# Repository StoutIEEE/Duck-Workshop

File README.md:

# Duck workshop

This repo is to archive the files required for the flashing duck workshop. The workshop's existence was at first an April fools day joke. It eventually became a real workshop.

In this repo you can find:
 + The eagle files for first and second version of circuit
 + The workshop presentation with notes
 + A BOM for the second version of the circuit (the final version)

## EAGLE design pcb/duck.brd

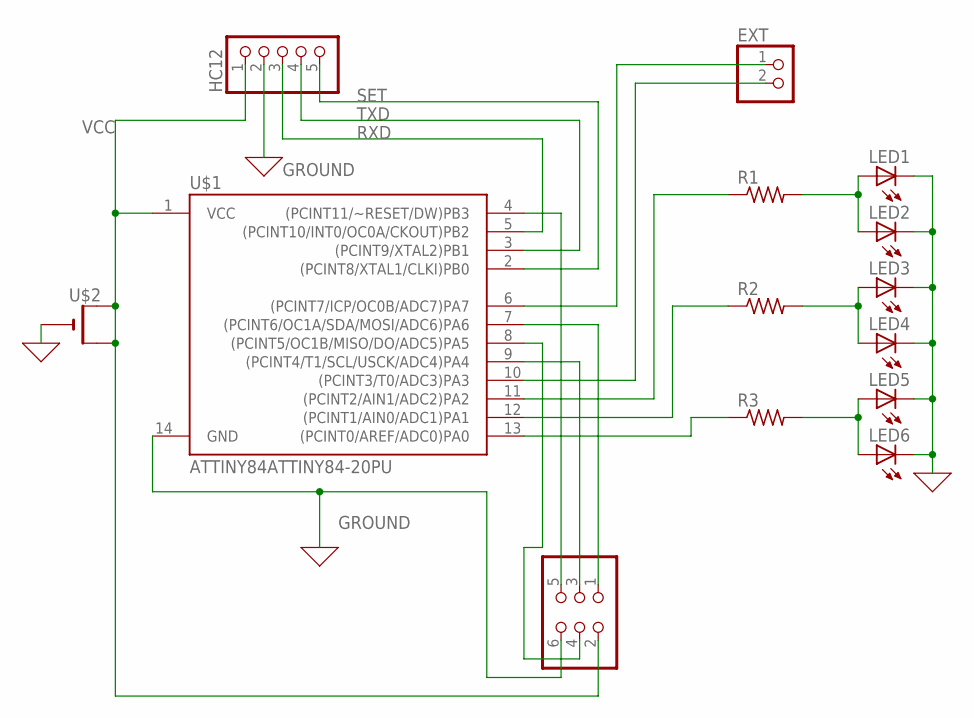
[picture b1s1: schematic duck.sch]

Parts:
DEV: PINHD-2X3; 2X03
EXT: PINHD-1X2; 1X02
HC12: PINHD-1X5; 1X05
LED1, LED2, LED3, LED4, LED5, LED6: LED3MM
R1, R2, R3: R-US_0204/7; 0204/7
U$1: ATTINY84ATTINY84-20PU; DIP14
U$2: CR1220THM; CR1220-THM

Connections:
GROUND: DEV.6, HC12.2, LED1.K (C), LED2.K (C), LED3.K (C), LED4.K (C), LED5.K (C), LED6.K (C), U$1.14 (GND), U$2.-
unnamed: DEV.1, U$1.7 ((PCINT6/OC1A/SDA/MOSI/ADC6)PA6)
unnamed: DEV.4, U$1.8 ((PCINT5/OC1B/MISO/DO/ADC5)PA5)
unnamed: DEV.3, U$1.9 ((PCINT4/T1/SCL/USCK/ADC4)PA4)
unnamed: R1.1, U$1.11 ((PCINT2/AIN1/ADC2)PA2)
unnamed: DEV.5, U$1.4 ((PCINT11/~RESET/DW)PB3)
unnamed: R2.1, U$1.12 ((PCINT1/AIN0/ADC1)PA1)
unnamed: R3.1, U$1.13 ((PCINT0/AREF/ADC0)PA0)
unnamed: EXT.1, U$1.6 ((PCINT7/ICP/OC0B/ADC7)PA7)
unnamed: LED1.A, LED2.A, R1.2
unnamed: LED3.A, LED4.A, R2.2
unnamed: EXT.2, U$1.10 ((PCINT3/T0/ADC3)PA3)
unnamed: LED5.A, LED6.A, R3.2
RXD: HC12.3, U$1.5 ((PCINT10/INT0/OC0A/CKOUT)PB2)
SET: HC12.5, U$1.2 ((PCINT8/XTAL1/CLKI)PB0)
TXD: HC12.4, U$1.3 ((PCINT9/XTAL2)PB1)
VCC: DEV.2, HC12.1, U$1.1 (VCC), U$2.+1 (+), U$2.+2 (+1)

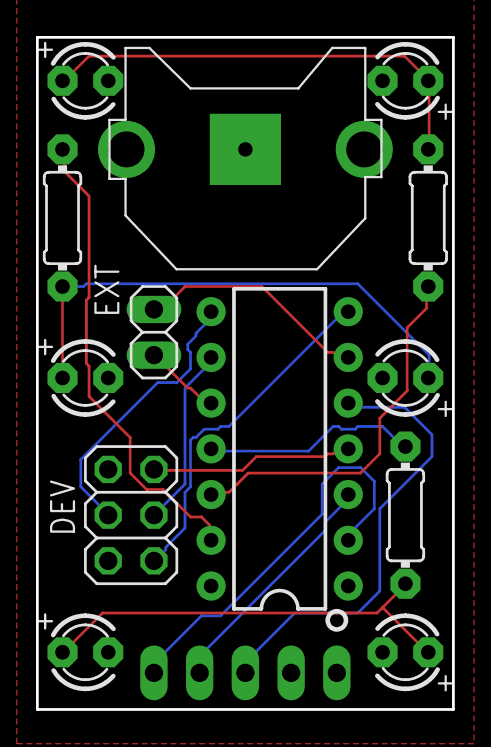
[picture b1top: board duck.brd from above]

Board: 2 copper layers, 23.1 x 37.3 mm, 14 parts (1 on the bottom side), 17 nets.

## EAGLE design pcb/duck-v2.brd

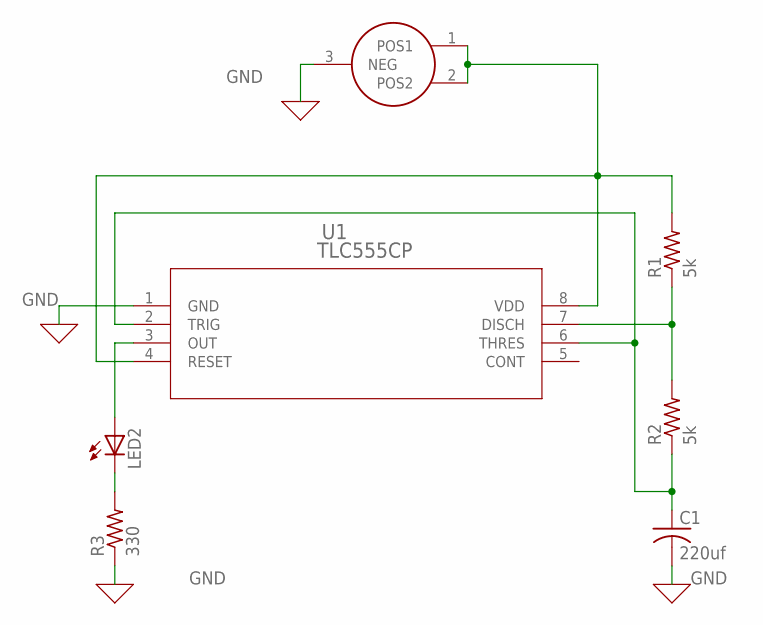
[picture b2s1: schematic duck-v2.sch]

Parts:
C1: 220uf; C025-024X044
LED2: LED5MM
R1, R2: 5k; 0204/7
R3: 330; 0204/7
U1: TLC555CP; P8
U$1: 2895

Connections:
GND: C1.2, R3.1, U1.1 (GND), U$1.3 (NEG)
unnamed: R1.1, R2.2, U1.7 (DISCH)
unnamed: LED2.A, U1.3 (OUT)
unnamed: C1.1, R2.1, U1.2 (TRIG), U1.6 (THRES)
unnamed: R1.2, U1.4 (RESET), U1.8 (VDD), U$1.1 (POS1), U$1.2 (POS2)
unnamed: LED2.K (C), R3.2

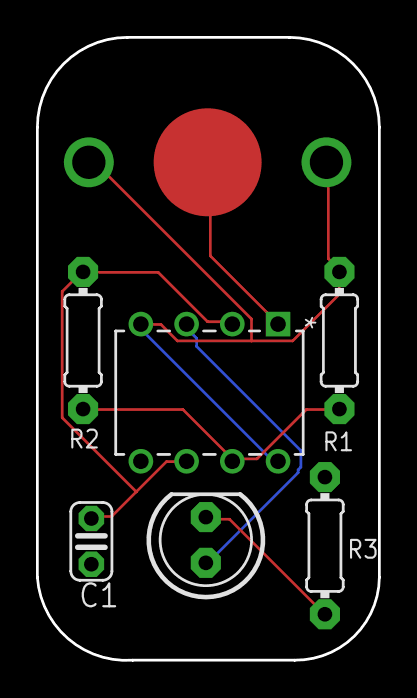
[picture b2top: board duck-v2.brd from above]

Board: 2 copper layers, 19.0 x 34.6 mm, 7 parts (0 on the bottom side), 6 nets.

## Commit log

2019-10-20 Initial
2019-10-29 Set up readme
2019-10-30 Add files
2019-10-30 Working
2019-11-04 Add presentation
2019-11-04 Add links

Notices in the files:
parts and their libraries:
SparkFun-IC-Microcontroller: Licensing: Creative Commons ShareAlike 4.0 International - https://creativecommons.org/licenses/by-sa/4.0
